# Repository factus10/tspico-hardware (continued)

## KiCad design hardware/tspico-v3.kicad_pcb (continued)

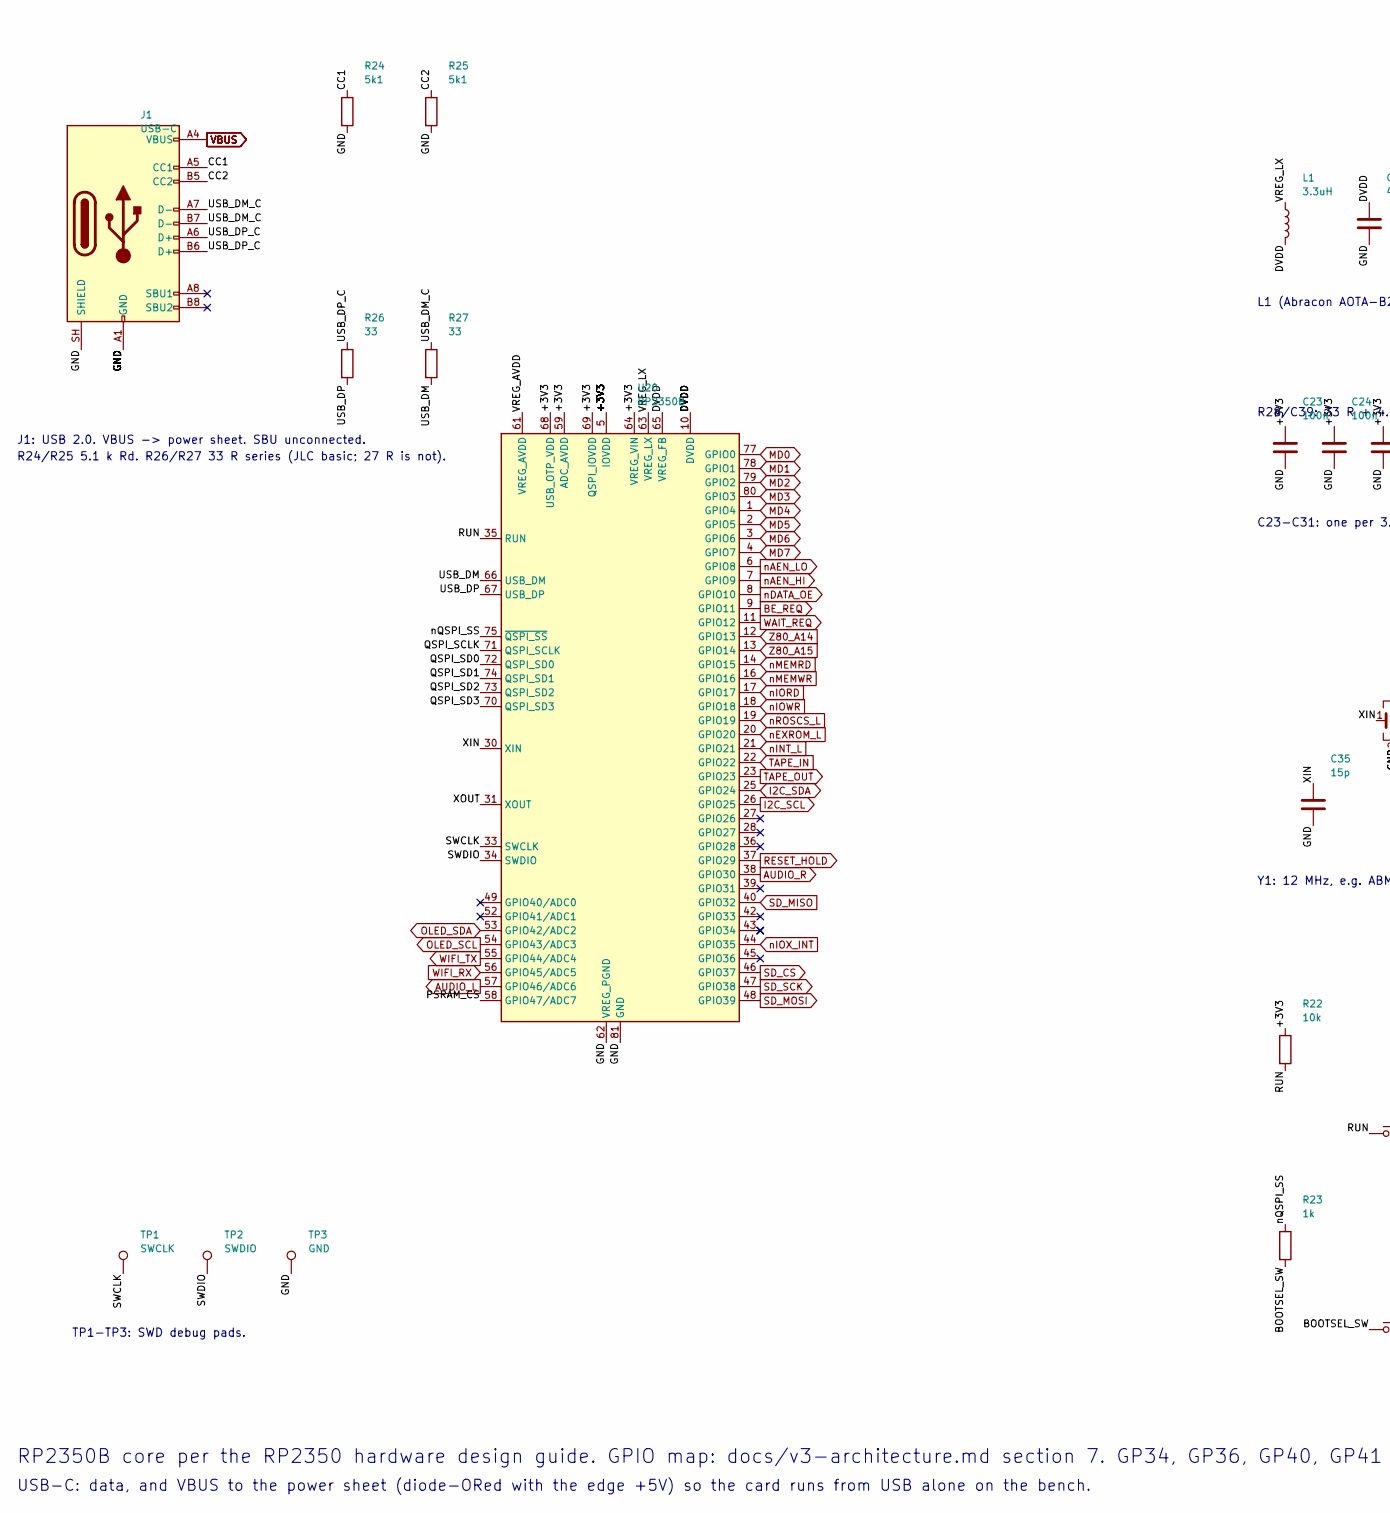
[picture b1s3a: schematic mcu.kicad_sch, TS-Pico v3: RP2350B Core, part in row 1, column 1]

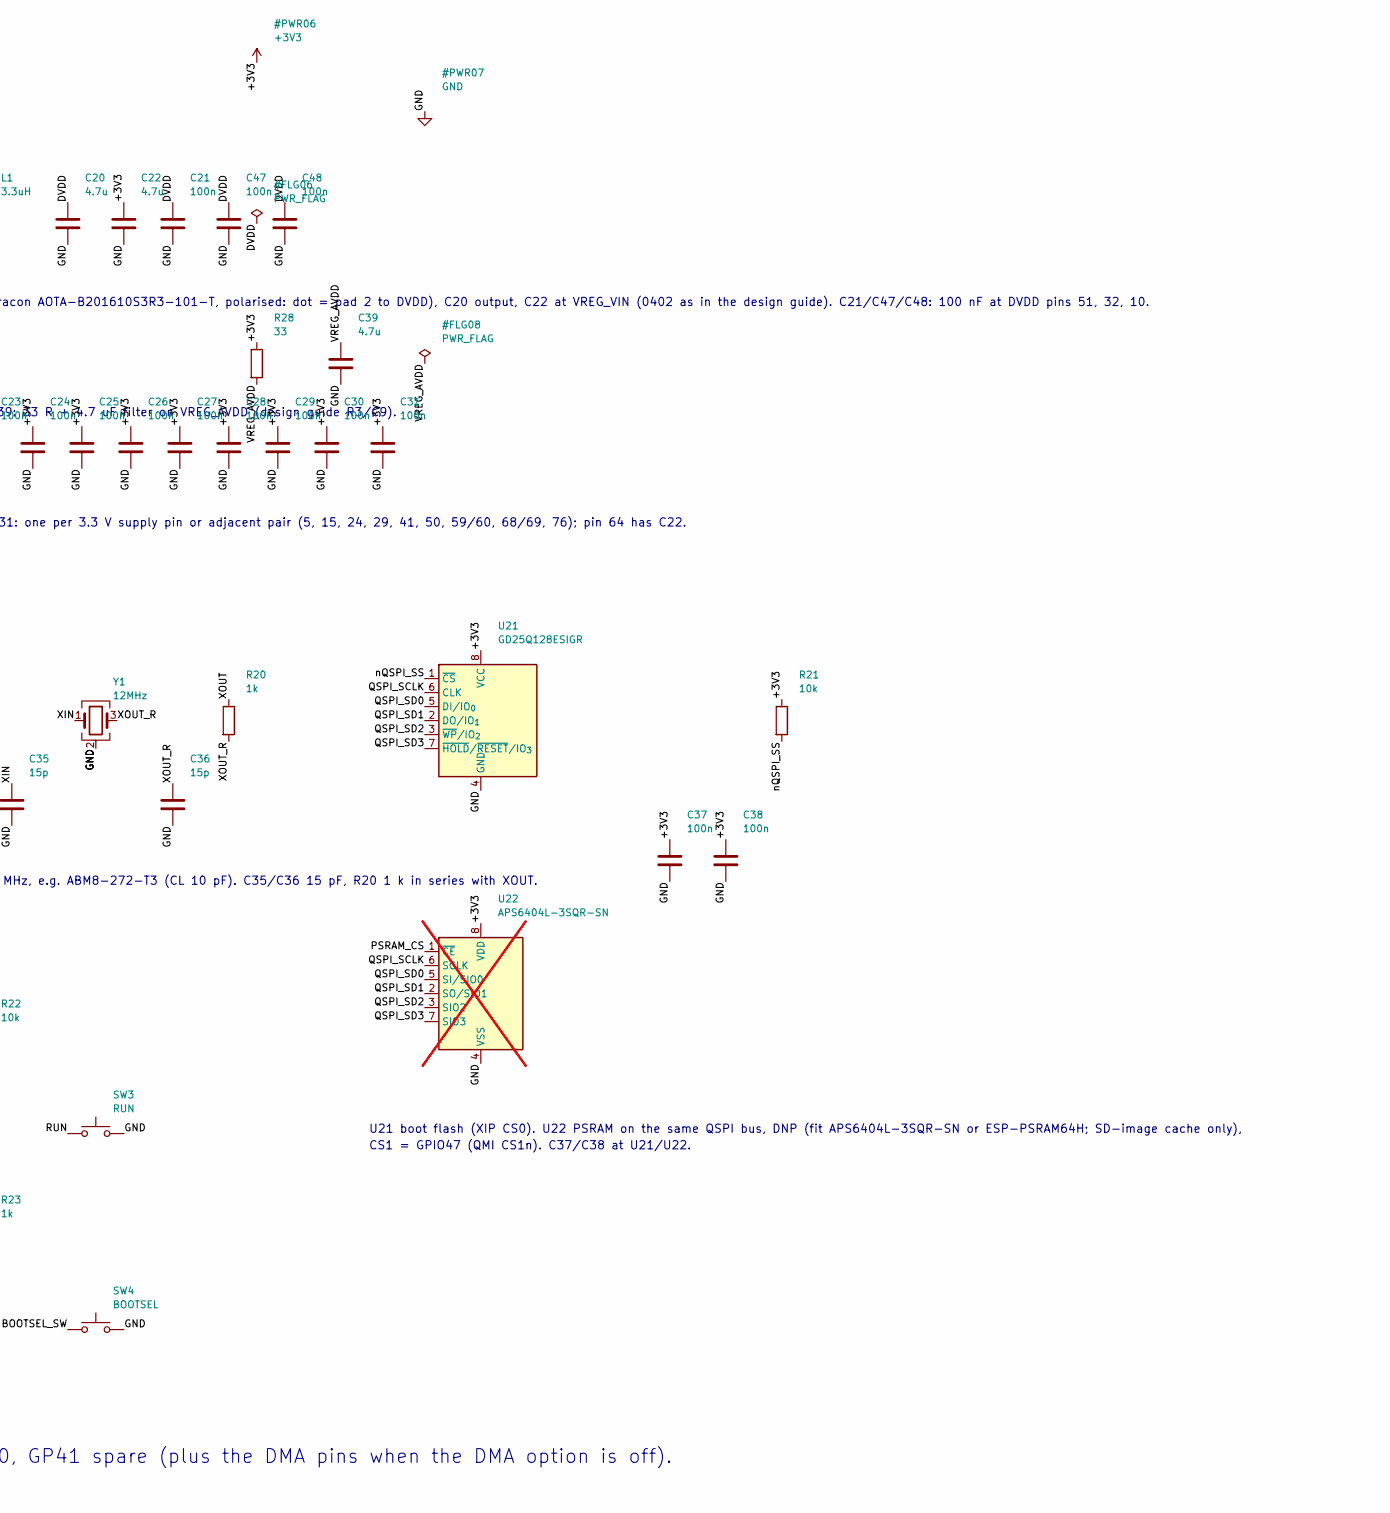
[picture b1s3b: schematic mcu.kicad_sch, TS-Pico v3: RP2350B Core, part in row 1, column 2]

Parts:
C20, C22, C39: 4.7u; C_0402_1005Metric; MPN CL05A475MP5NRNC; LCSC C23733
C21, C23, C24, C25, C26, C27, C28, C29, C30, C31, C37, C38, C47, C48: 100n; C_0603_1608Metric; MPN CC0603KRX7R9BB104; LCSC C14663
C35, C36: 15p; C_0603_1608Metric; MPN CL10C150JB8NNNC; LCSC C1644
J1: USB-C; USB_C_Receptacle_HRO_TYPE-C-31-M-12; MPN TYPE-C-31-M-12; LCSC C165948
L1: 3.3uH; L_Abracon_AOTA-B201610; MPN AOTA-B201610S3R3-101-T; LCSC C42411119
R20, R23: 1k; R_0603_1608Metric; MPN 0603WAF1001T5E; LCSC C21190
R21, R22: 10k; R_0603_1608Metric; MPN 0603WAF1002T5E; LCSC C25804
R24, R25: 5k1; R_0603_1608Metric; MPN 0603WAF5101T5E; LCSC C23186
R26, R27, R28: 33; R_0603_1608Metric; MPN 0603WAF330JT5E; LCSC C23140
SW3: RUN; SW_Push_1P1T_XKB_TS-1187A; MPN TS-1187A-B-A-B; LCSC C318884
SW4: BOOTSEL; SW_Push_1P1T_XKB_TS-1187A; MPN TS-1187A-B-A-B; LCSC C318884
TP1: SWCLK; TestPoint_Pad_1.5x1.5mm
TP2: SWDIO; TestPoint_Pad_1.5x1.5mm
TP3: GND; TestPoint_Pad_1.5x1.5mm
U20: RP2350B; QFN-80-1EP_10x10mm_P0.4mm_EP3.4x3.4mm; MPN RP2350B; LCSC C42415655
U21: GD25Q128ESIGR; SOIC-8_5.3x5.3mm_P1.27mm; MPN GD25Q128ESIGR; LCSC C2928891
U22: APS6404L-3SQR-SN; SOIC-8_3.9x4.9mm_P1.27mm; MPN APS6404L-3SQR-SN; LCSC C5333729; not fitted
Y1: 12MHz; Crystal_SMD_3225-4Pin_3.2x2.5mm; MPN ABM8-272-T3; LCSC C20625731

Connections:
+3V3: C22.1, C23.1, C24.1, C25.1, C26.1, C27.1, C28.1, C29.1, C30.1, C31.1, C37.1, C38.1, R21.1, R22.1, R28.1, U20.5 (IOVDD), U20.15 (IOVDD), U20.24 (IOVDD), U20.29 (IOVDD), U20.41 (IOVDD), U20.50 (IOVDD), U20.59 (ADC_AVDD), U20.60 (IOVDD), U20.64 (VREG_VIN), U20.68 (USB_OTP_VDD), U20.69 (QSPI_IOVDD), U20.76 (IOVDD), U21.8 (VCC), U22.8 (VDD); also elsewhere on the board
/RP2350B Core/BOOTSEL_SW: R23.2, SW4.1
/RP2350B Core/CC1: J1.A5 (CC1), R24.1
/RP2350B Core/CC2: J1.B5 (CC2), R25.1
/RP2350B Core/PSRAM_CS: U20.58 (GPIO47/ADC7), U22.1 (~CE)
/RP2350B Core/QSPI_SCLK: U20.71 (QSPI_SCLK), U21.6 (CLK), U22.6 (SCLK)
/RP2350B Core/QSPI_SD0: U20.72 (QSPI_SD0), U21.5 (DI/IO_{0}), U22.5 (SI/SIO0)
/RP2350B Core/QSPI_SD1: U20.74 (QSPI_SD1), U21.2 (DO/IO_{1}), U22.2 (SO/SIO1)
/RP2350B Core/QSPI_SD2: U20.73 (QSPI_SD2), U21.3 (~WP/IO_{2}), U22.3 (SIO2)
/RP2350B Core/QSPI_SD3: U20.70 (QSPI_SD3), U21.7 (~HOLD/~RESET/IO_{3}), U22.7 (SIO3)
/RP2350B Core/RUN: R22.2, SW3.1, U20.35 (RUN)
/RP2350B Core/SWCLK: TP1.1, U20.33 (SWCLK)
/RP2350B Core/SWDIO: TP2.1, U20.34 (SWDIO)
/RP2350B Core/USB_DM: R27.2, U20.66 (USB_DM)
/RP2350B Core/USB_DM_C: J1.A7 (D-), J1.B7 (D-), R27.1
/RP2350B Core/USB_DP: R26.2, U20.67 (USB_DP)
/RP2350B Core/USB_DP_C: J1.A6 (D+), J1.B6 (D+), R26.1
/RP2350B Core/VREG_AVDD: C39.1, R28.2, U20.61 (VREG_AVDD)
/RP2350B Core/XIN: C35.1, U20.30 (XIN), Y1.1
/RP2350B Core/XOUT: R20.1, U20.31 (XOUT)
/RP2350B Core/XOUT_R: C36.1, R20.2, Y1.3
/RP2350B Core/nQSPI_SS: R21.2, R23.1, U20.75 (~QSPI_SS), U21.1 (~CS)
AUDIO_L: U20.57 (GPIO46/ADC6); also elsewhere on the board
AUDIO_R: U20.38 (GPIO30); also elsewhere on the board
BE_REQ: U20.9 (GPIO11); also elsewhere on the board
I2C_SCL: U20.26 (GPIO25); also elsewhere on the board
I2C_SDA: U20.25 (GPIO24); also elsewhere on the board
MD0: U20.77 (GPIO0); also elsewhere on the board
MD1: U20.78 (GPIO1); also elsewhere on the board
MD2: U20.79 (GPIO2); also elsewhere on the board
MD3: U20.80 (GPIO3); also elsewhere on the board
MD4: U20.1 (GPIO4); also elsewhere on the board
MD5: U20.2 (GPIO5); also elsewhere on the board
MD6: U20.3 (GPIO6); also elsewhere on the board
MD7: U20.4 (GPIO7); also elsewhere on the board
unnamed: L1.1, U20.63 (VREG_LX)
OLED_SCL: U20.54 (GPIO43/ADC3); also elsewhere on the board
OLED_SDA: U20.53 (GPIO42/ADC2); also elsewhere on the board
RESET_HOLD: U20.37 (GPIO29); also elsewhere on the board
SD_CS: U20.46 (GPIO37); also elsewhere on the board
SD_MISO: U20.40 (GPIO32); also elsewhere on the board
SD_MOSI: U20.48 (GPIO39); also elsewhere on the board
SD_SCK: U20.47 (GPIO38); also elsewhere on the board
TAPE_IN: U20.22 (GPIO22); also elsewhere on the board
TAPE_OUT: U20.23 (GPIO23); also elsewhere on the board
VBUS: J1.A4 (VBUS), J1.A9 (VBUS), J1.B4 (VBUS), J1.B9 (VBUS); also elsewhere on the board
WAIT_REQ: U20.11 (GPIO12); also elsewhere on the board
WIFI_RX: U20.56 (GPIO45/ADC5); also elsewhere on the board
WIFI_TX: U20.55 (GPIO44/ADC4); also elsewhere on the board
Z80_A14: U20.12 (GPIO13); also elsewhere on the board
Z80_A15: U20.13 (GPIO14); also elsewhere on the board
nAEN_HI: U20.7 (GPIO9); also elsewhere on the board
nAEN_LO: U20.6 (GPIO8); also elsewhere on the board
nDATA_OE: U20.8 (GPIO10); also elsewhere on the board
nEXROM_L: U20.20 (GPIO20); also elsewhere on the board
nINT_L: U20.21 (GPIO21); also elsewhere on the board
nIORD: U20.17 (GPIO17); also elsewhere on the board
nIOWR: U20.18 (GPIO18); also elsewhere on the board
nIOX_INT: U20.44 (GPIO35); also elsewhere on the board
nMEMRD: U20.14 (GPIO15); also elsewhere on the board
nMEMWR: U20.16 (GPIO16); also elsewhere on the board
nROSCS_L: U20.19 (GPIO19); also elsewhere on the board

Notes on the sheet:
RP2350B core per the RP2350 hardware design guide. GPIO map: docs/v3-architecture.md section 7. GP34, GP36, GP40, GP41 spare (plus the DMA pins when the DMA option is off).
USB-C: data, and VBUS to the power sheet (diode-ORed with the edge +5V) so the card runs from USB alone on the bench.
L1 (Abracon AOTA-B201610S3R3-101-T, polarised: dot = pad 2 to DVDD), C20 output, C22 at VREG_VIN (0402 as in the design guide). C21/C47/C48: 100 nF at DVDD pins 51, 32, 10.
R28/C39: 33 R + 4.7 uF filter on VREG_AVDD (design guide R3/C9).
C23-C31: one per 3.3 V supply pin or adjacent pair (5, 15, 24, 29, 41, 50, 59/60, 68/69, 76); pin 64 has C22.
Y1: 12 MHz, e.g. ABM8-272-T3 (CL 10 pF). C35/C36 15 pF, R20 1 k in series with XOUT.
U21 boot flash (XIP CS0). U22 PSRAM on the same QSPI bus, DNP (fit APS6404L-3SQR-SN or ESP-PSRAM64H; SD-image cache only),
CS1 = GPIO47 (QMI CS1n). C37/C38 at U21/U22.
J1: USB 2.0. VBUS -> power sheet. SBU unconnected.
R24/R25 5.1 k Rd. R26/R27 33 R series (JLC basic; 27 R is not).
TP1-TP3: SWD debug pads.

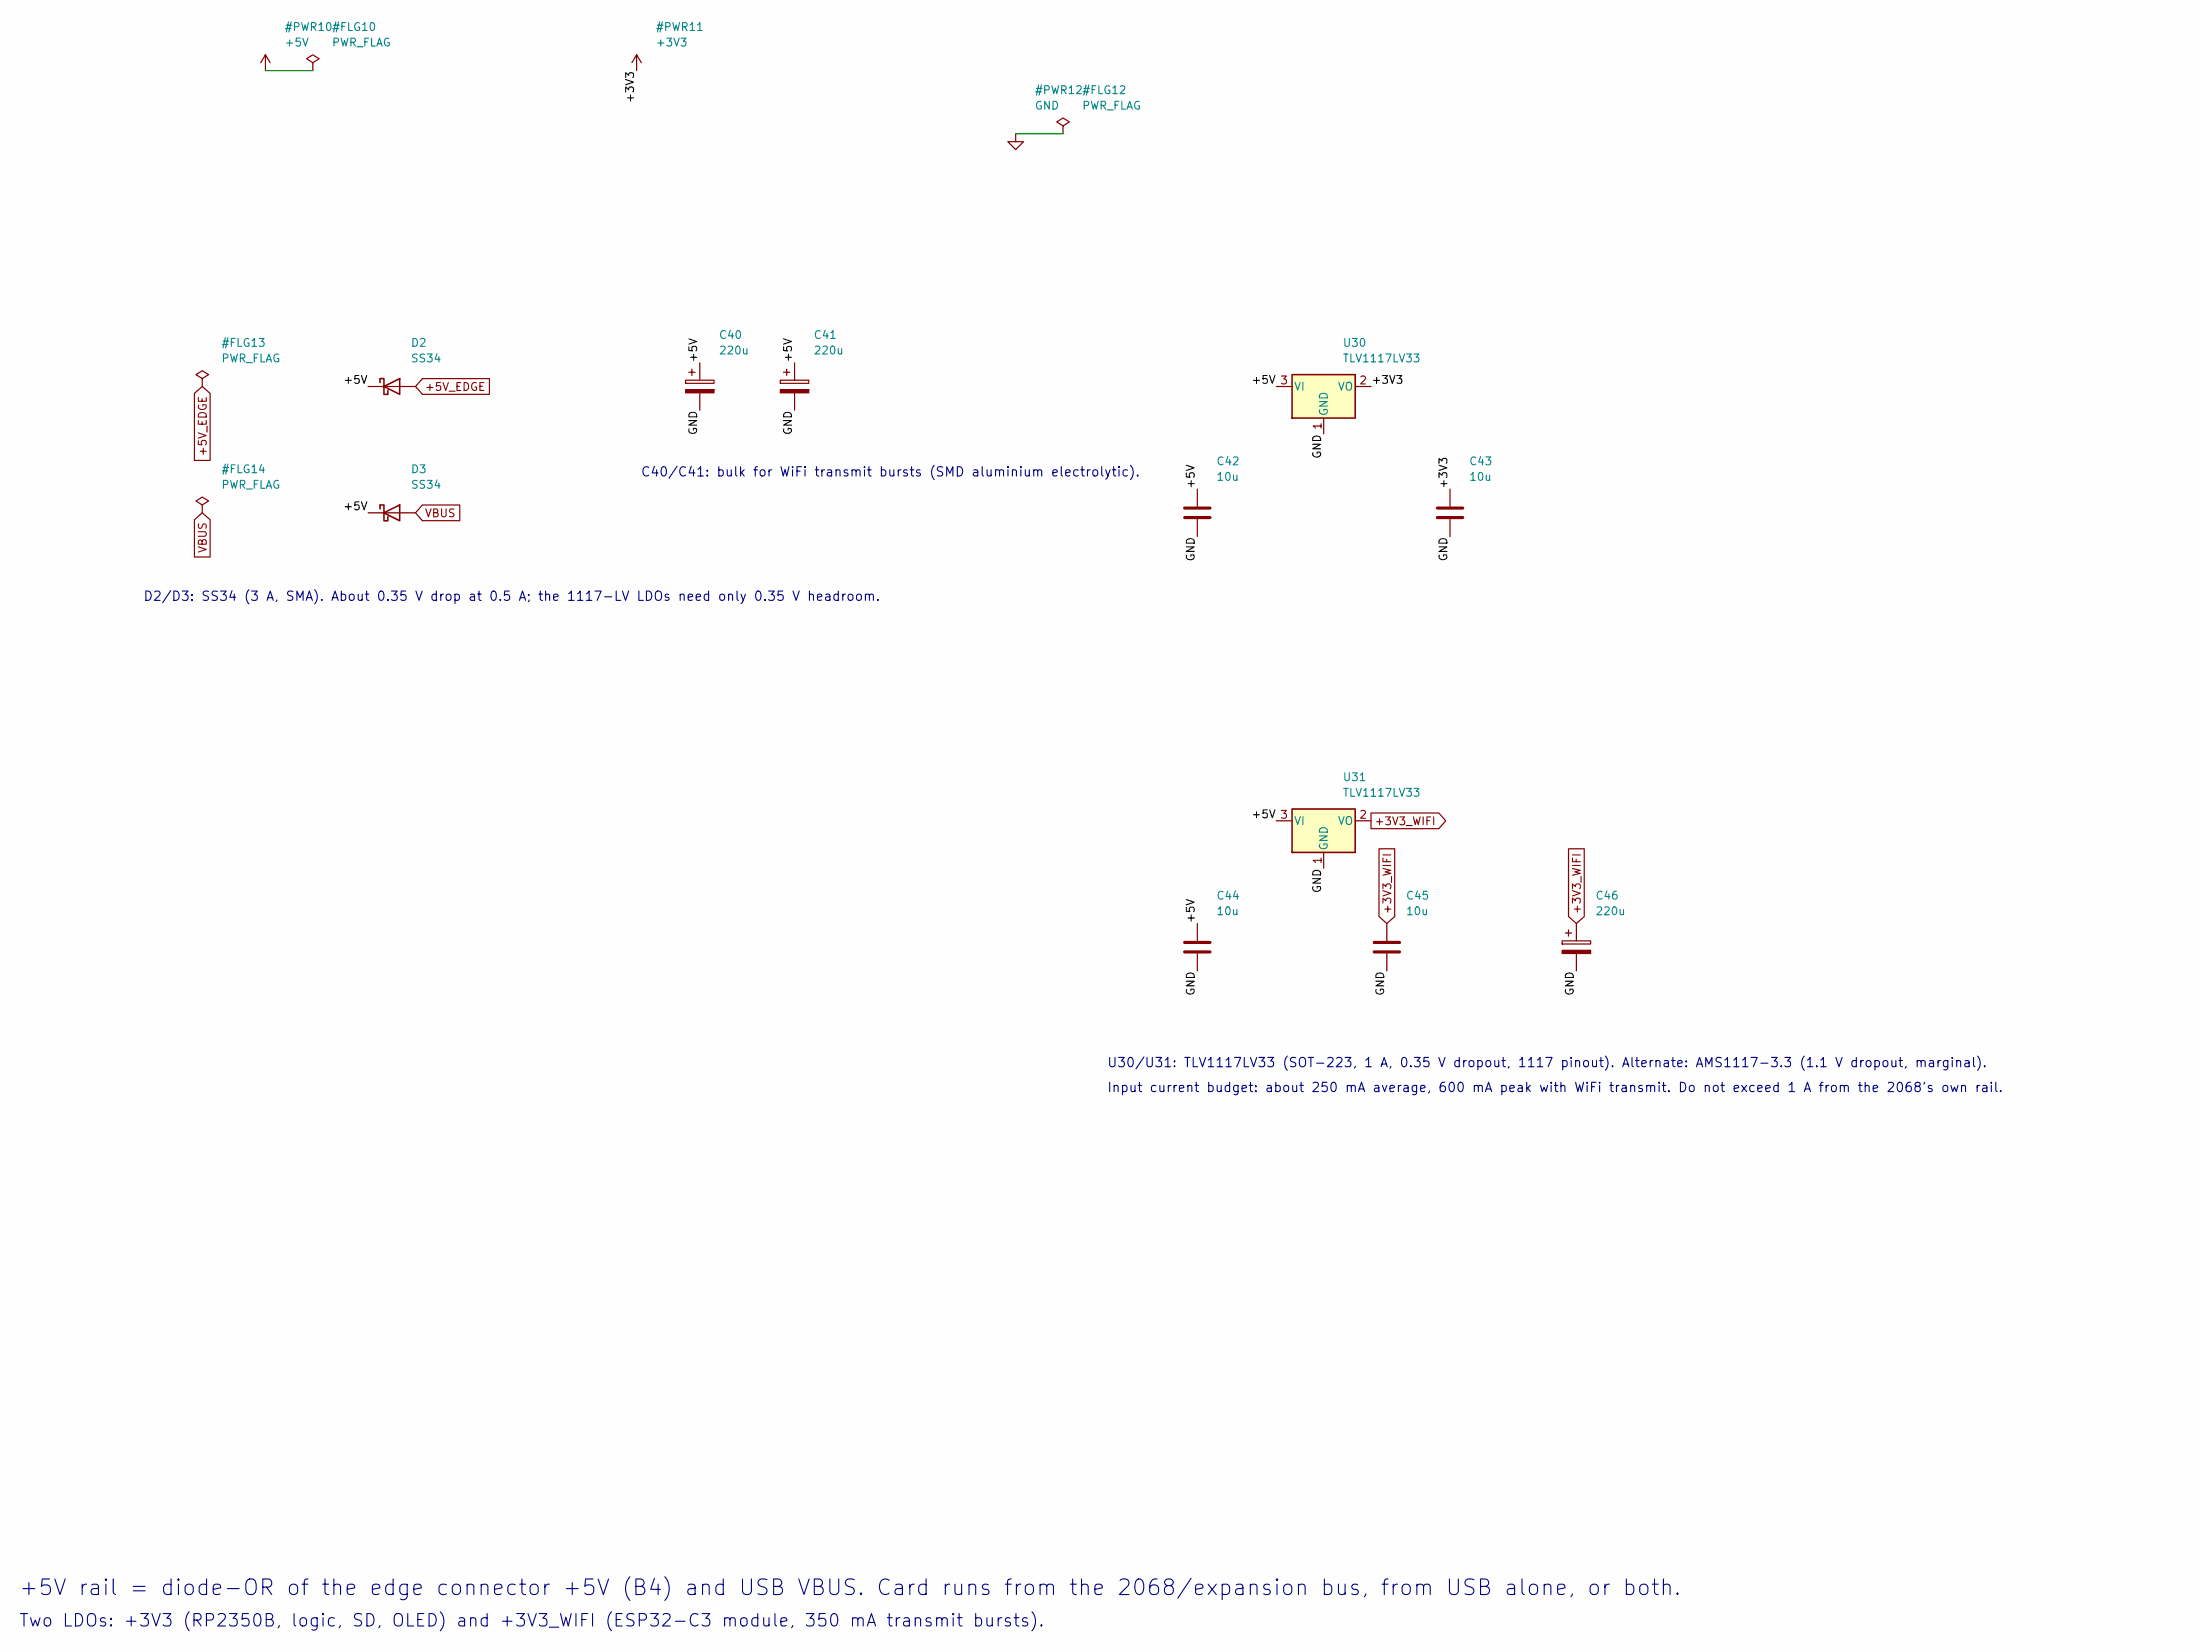
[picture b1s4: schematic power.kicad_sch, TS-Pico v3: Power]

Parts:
C40, C41, C46: 220u; CP_Elec_6.3x5.4; MPN RVT220UF10V67RV0037; LCSC C2833309
C42, C43, C44, C45: 10u; C_0603_1608Metric; MPN CL10A106KP8NNNC; LCSC C19702
D2, D3: SS34; D_SMA; MPN SS34; LCSC C8678
U30, U31: TLV1117LV33; SOT-223-3_TabPin2; MPN TLV1117LV33DCYR; LCSC C15578

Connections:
+3V3: C43.1, U30.2 (VO); also elsewhere on the board
+3V3_WIFI: C45.1, C46.1, U31.2 (VO); also elsewhere on the board
+5V: C40.1, C41.1, C42.1, C44.1, D2.1 (K), D3.1 (K), U30.3 (VI), U31.3 (VI); also elsewhere on the board
+5V_EDGE: D2.2 (A); also elsewhere on the board
VBUS: D3.2 (A); also elsewhere on the board

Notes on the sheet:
+5V rail = diode-OR of the edge connector +5V (B4) and USB VBUS. Card runs from the 2068/expansion bus, from USB alone, or both.
Two LDOs: +3V3 (RP2350B, logic, SD, OLED) and +3V3_WIFI (ESP32-C3 module, 350 mA transmit bursts).
D2/D3: SS34 (3 A, SMA). About 0.35 V drop at 0.5 A; the 1117-LV LDOs need only 0.35 V headroom.
C40/C41: bulk for WiFi transmit bursts (SMD aluminium electrolytic).
U30/U31: TLV1117LV33 (SOT-223, 1 A, 0.35 V dropout, 1117 pinout). Alternate: AMS1117-3.3 (1.1 V dropout, marginal).
Input current budget: about 250 mA average, 600 mA peak with WiFi transmit. Do not exceed 1 A from the 2068's own rail.

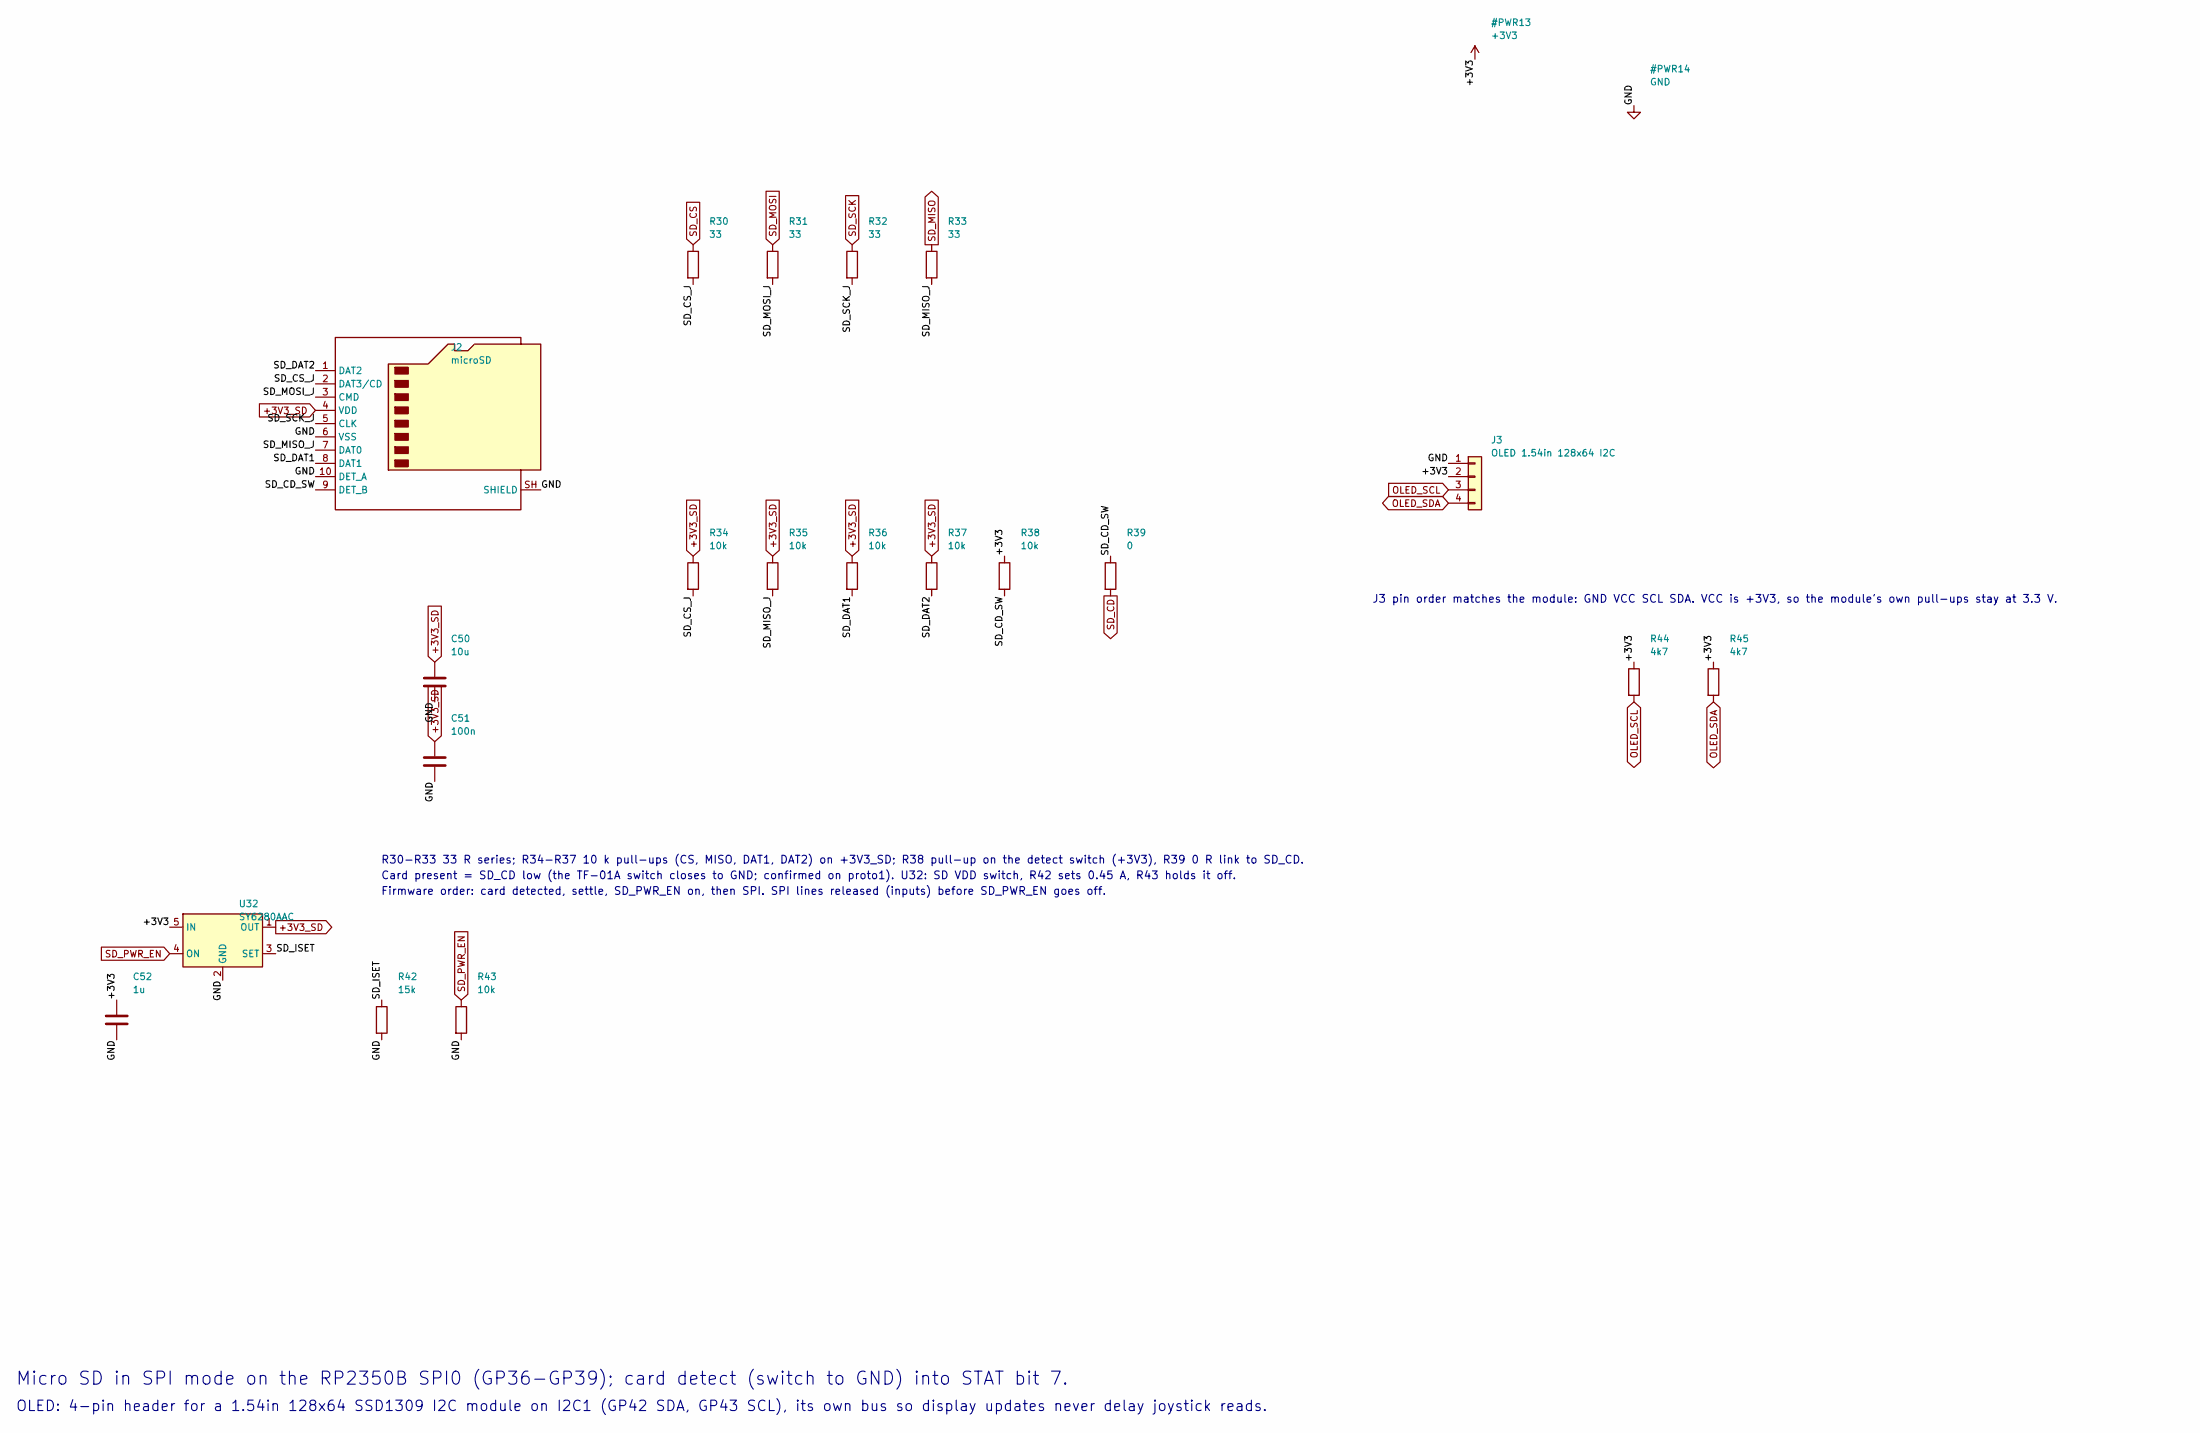
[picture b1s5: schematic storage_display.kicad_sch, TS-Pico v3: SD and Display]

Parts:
C50: 10u; C_0603_1608Metric; MPN CL10A106KP8NNNC; LCSC C19702
C51: 100n; C_0603_1608Metric; MPN CC0603KRX7R9BB104; LCSC C14663
C52: 1u; C_0603_1608Metric; MPN CL10A105KB8NNNC; LCSC C15849
J2: microSD; microSD_TF-01A; MPN TF-01A; LCSC C91145
J3: OLED 1.54in 128x64 I2C; PinHeader_1x04_P2.54mm_Vertical; MPN 2.54-1x40P (cut to 4); LCSC C2337
R30, R31, R32, R33: 33; R_0603_1608Metric; MPN 0603WAF330JT5E; LCSC C23140
R34, R35, R36, R37, R38, R43: 10k; R_0603_1608Metric; MPN 0603WAF1002T5E; LCSC C25804
R39: 0; R_0603_1608Metric; MPN 0603WAF0000T5E; LCSC C21189
R42: 15k; R_0603_1608Metric; MPN 0603WAF1502T5E; LCSC C22809
R44, R45: 4k7; R_0603_1608Metric; MPN 0603WAF4701T5E; LCSC C23162
U32: SY6280AAC; SOT-23-5; MPN SY6280AAC; LCSC C55136

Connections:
+3V3: C52.1, J3.2, R38.1, R44.1, R45.1, U32.5 (IN); also elsewhere on the board
+3V3_SD: C50.1, C51.1, J2.4 (VDD), R34.1, R35.1, R36.1, R37.1, U32.1 (OUT)
/SD and Display/SD_CD_SW: J2.9 (DET_B), R38.2, R39.1
/SD and Display/SD_CS_J: J2.2 (DAT3/CD), R30.2, R34.2
/SD and Display/SD_DAT1: J2.8 (DAT1), R36.2
/SD and Display/SD_DAT2: J2.1 (DAT2), R37.2
/SD and Display/SD_ISET: R42.1, U32.3 (SET)
/SD and Display/SD_MISO_J: J2.7 (DAT0), R33.2, R35.2
/SD and Display/SD_MOSI_J: J2.3 (CMD), R31.2
/SD and Display/SD_SCK_J: J2.5 (CLK), R32.2
OLED_SCL: J3.3, R44.2; also elsewhere on the board
OLED_SDA: J3.4, R45.2; also elsewhere on the board
SD_CD: R39.2; also elsewhere on the board
SD_CS: R30.1; also elsewhere on the board
SD_MISO: R33.1; also elsewhere on the board
SD_MOSI: R31.1; also elsewhere on the board
SD_PWR_EN: R43.1, U32.4 (ON); also elsewhere on the board
SD_SCK: R32.1; also elsewhere on the board

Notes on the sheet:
Micro SD in SPI mode on the RP2350B SPI0 (GP36-GP39); card detect (switch to GND) into STAT bit 7.
OLED: 4-pin header for a 1.54in 128x64 SSD1309 I2C module on I2C1 (GP42 SDA, GP43 SCL), its own bus so display updates never delay joystick reads.
R30-R33 33 R series; R34-R37 10 k pull-ups (CS, MISO, DAT1, DAT2) on +3V3_SD; R38 pull-up on the detect switch (+3V3), R39 0 R link to SD_CD.
Card present = SD_CD low (the TF-01A switch closes to GND; confirmed on proto1). U32: SD VDD switch, R42 sets 0.45 A, R43 holds it off.
Firmware order: card detected, settle, SD_PWR_EN on, then SPI. SPI lines released (inputs) before SD_PWR_EN goes off.
J3 pin order matches the module: GND VCC SCL SDA. VCC is +3V3, so the module's own pull-ups stay at 3.3 V.

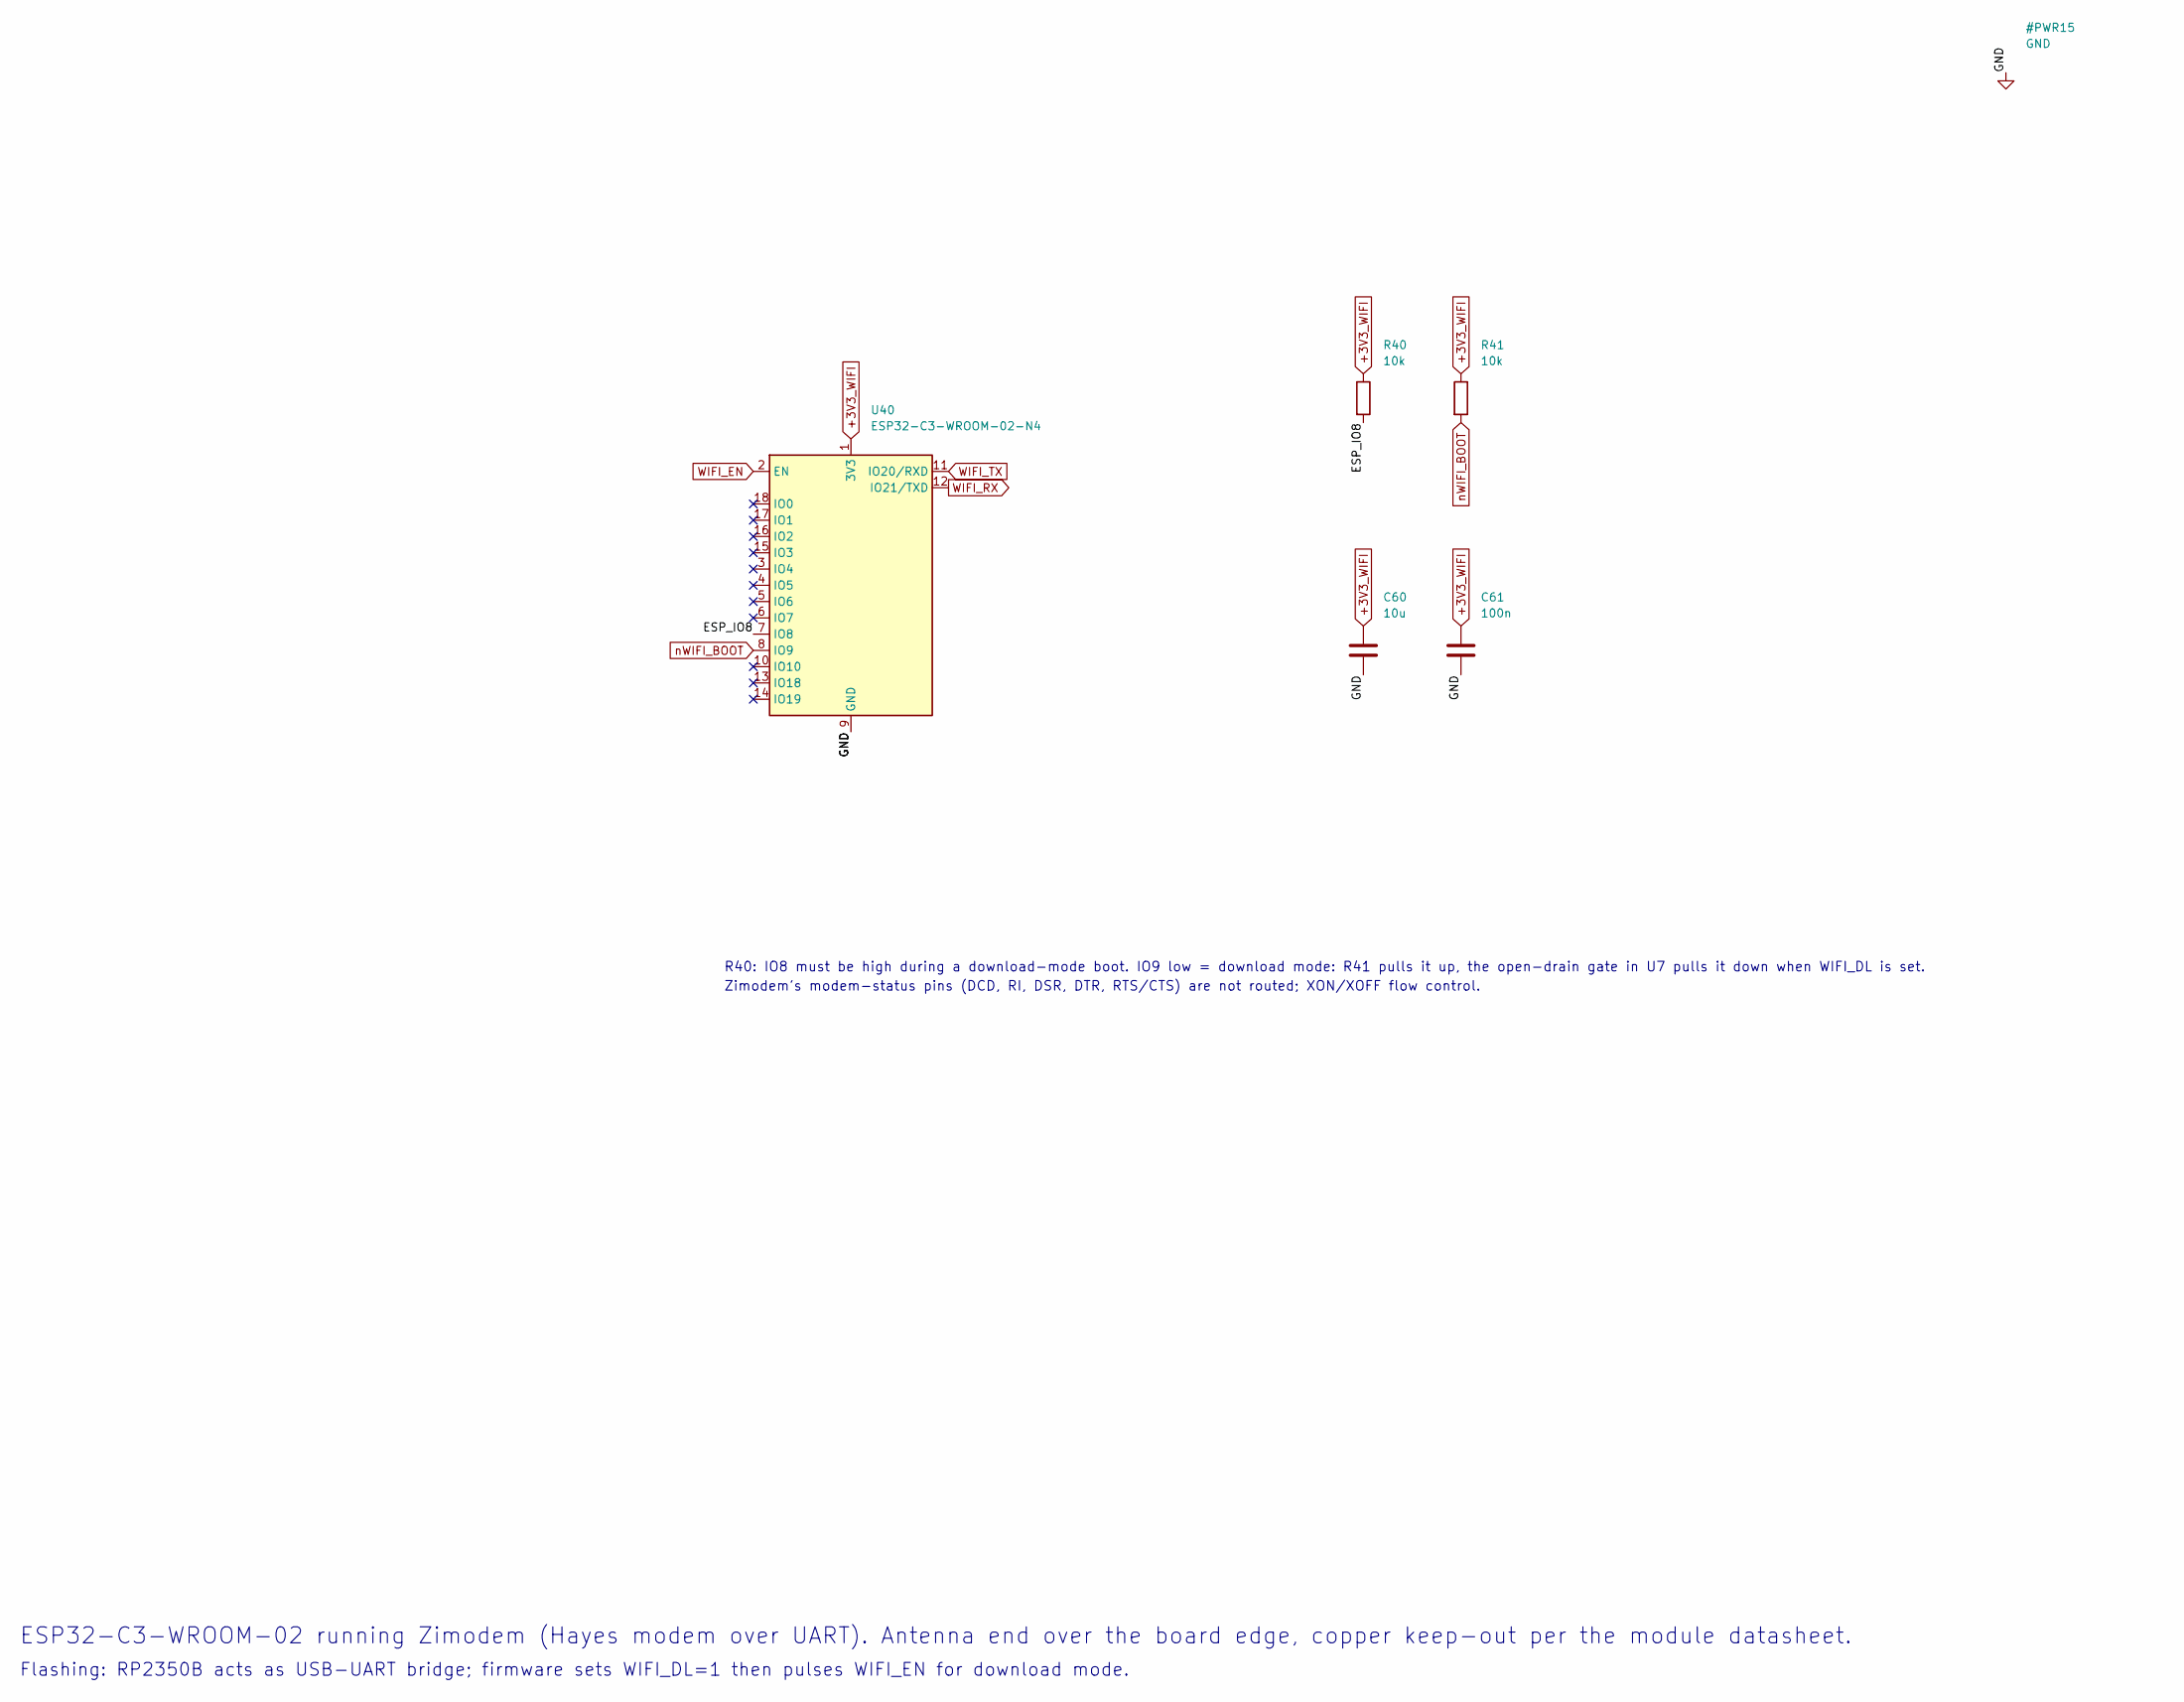
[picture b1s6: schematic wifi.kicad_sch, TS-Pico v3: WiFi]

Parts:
C60: 10u; C_0603_1608Metric; MPN CL10A106KP8NNNC; LCSC C19702
C61: 100n; C_0603_1608Metric; MPN CC0603KRX7R9BB104; LCSC C14663
R40, R41: 10k; R_0603_1608Metric; MPN 0603WAF1002T5E; LCSC C25804
U40: ESP32-C3-WROOM-02-N4; ESP32-C3-WROOM-02; MPN ESP32-C3-WROOM-02-N4; LCSC C2934560

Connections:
+3V3_WIFI: C60.1, C61.1, R40.1, R41.1, U40.1 (3V3); also elsewhere on the board
/WiFi/ESP_IO8: R40.2, U40.7 (IO8)
WIFI_EN: U40.2 (EN); also elsewhere on the board
WIFI_RX: U40.12 (IO21/TXD); also elsewhere on the board
WIFI_TX: U40.11 (IO20/RXD); also elsewhere on the board
nWIFI_BOOT: R41.2, U40.8 (IO9); also elsewhere on the board

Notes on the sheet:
ESP32-C3-WROOM-02 running Zimodem (Hayes modem over UART). Antenna end over the board edge, copper keep-out per the module datasheet.
Flashing: RP2350B acts as USB-UART bridge; firmware sets WIFI_DL=1 then pulses WIFI_EN for download mode.
R40: IO8 must be high during a download-mode boot. IO9 low = download mode: R41 pulls it up, the open-drain gate in U7 pulls it down when WIFI_DL is set.
Zimodem's modem-status pins (DCD, RI, DSR, DTR, RTS/CTS) are not routed; XON/XOFF flow control.
